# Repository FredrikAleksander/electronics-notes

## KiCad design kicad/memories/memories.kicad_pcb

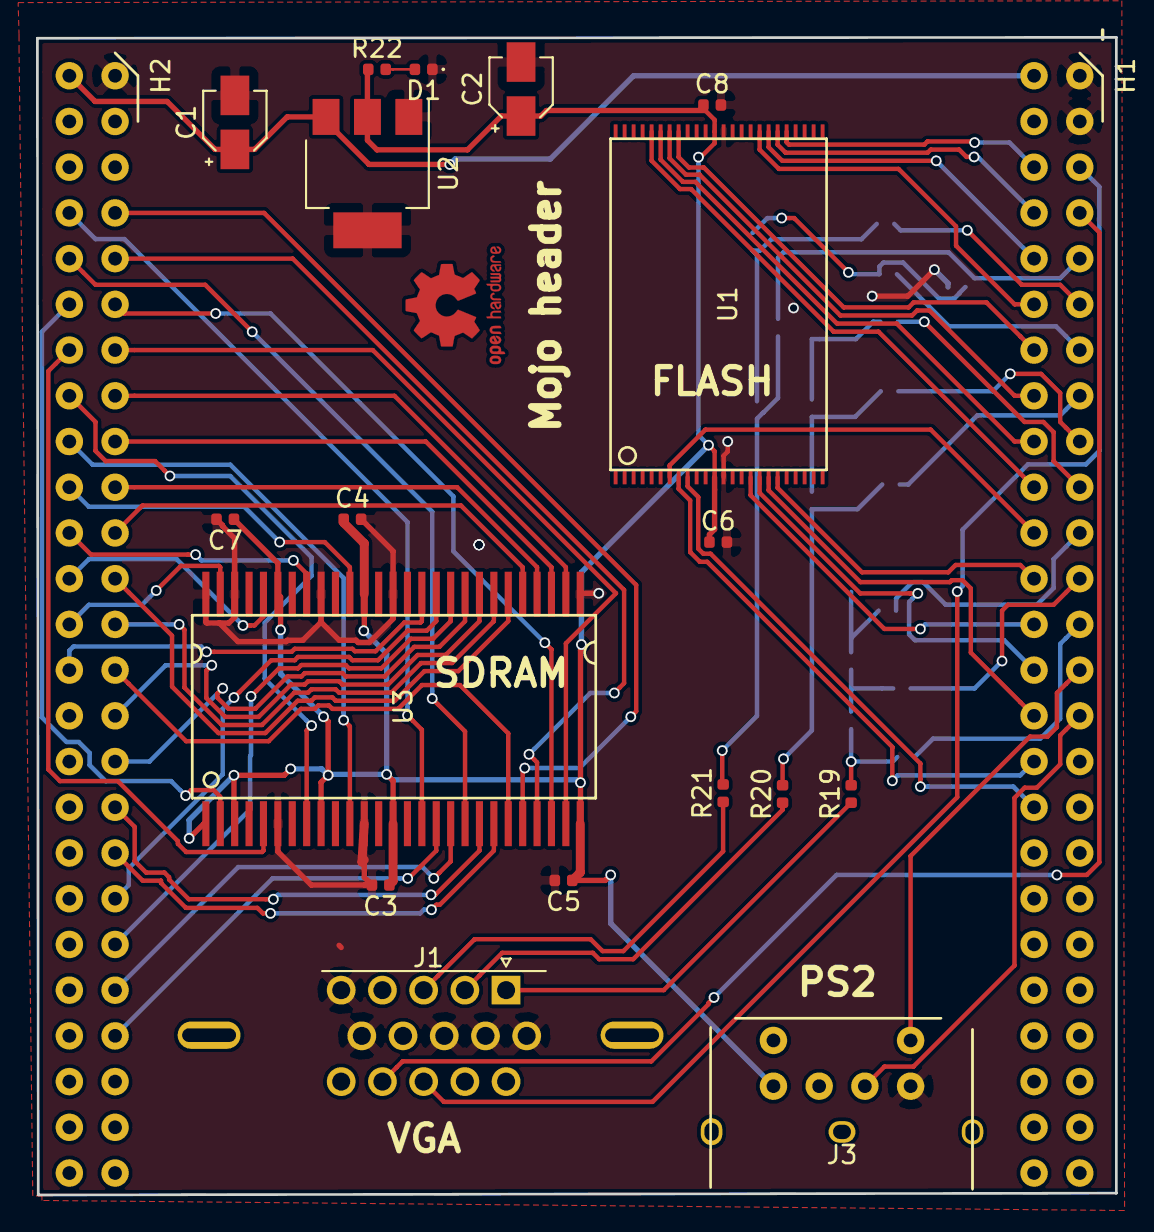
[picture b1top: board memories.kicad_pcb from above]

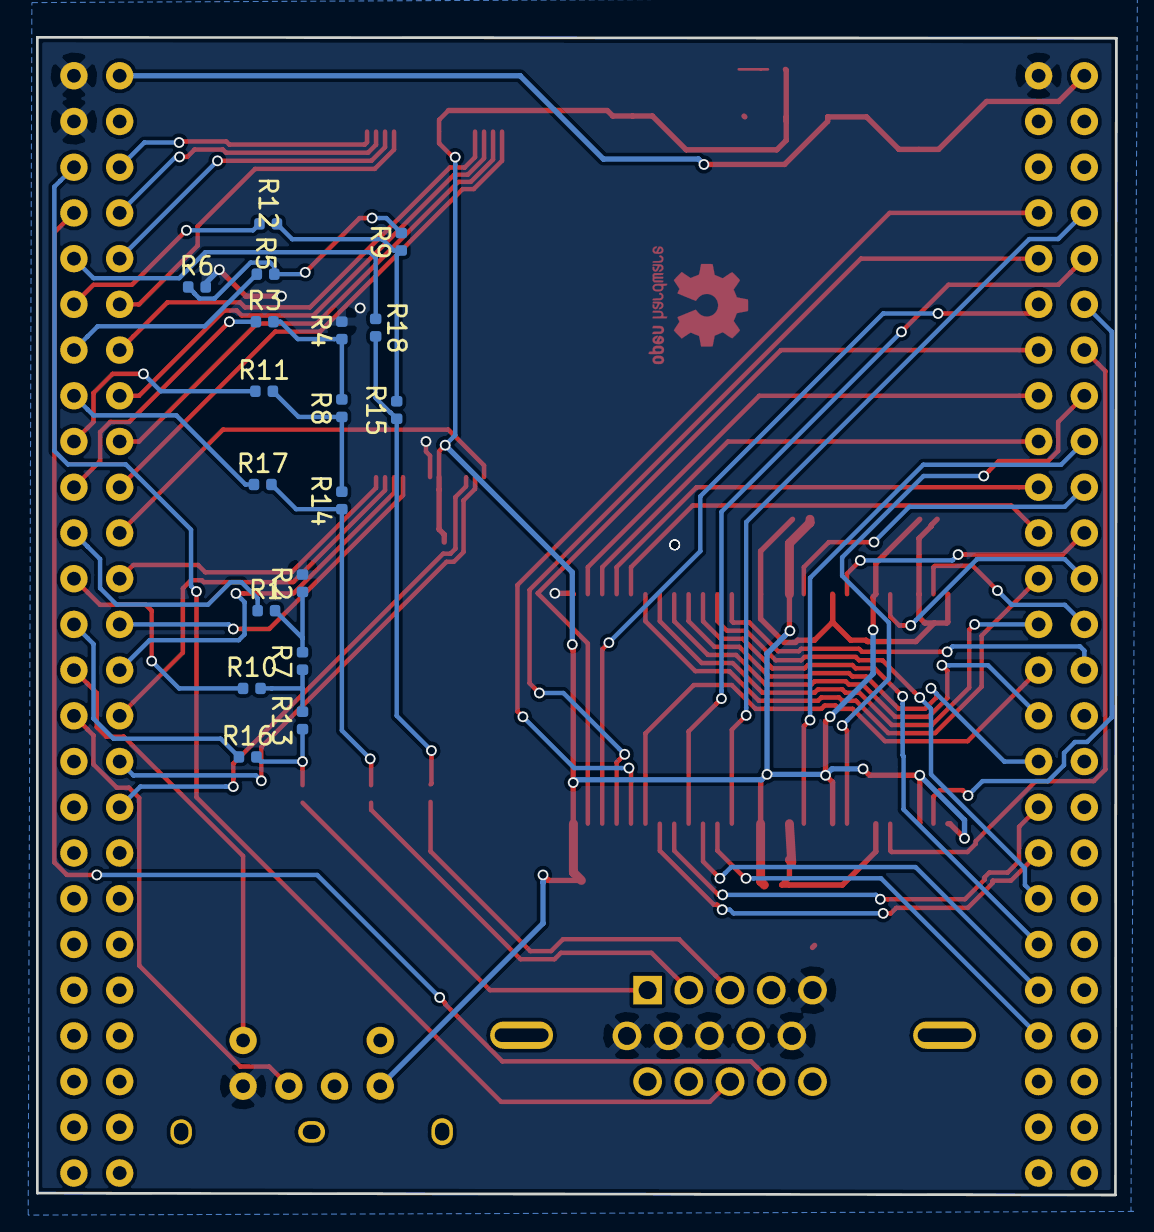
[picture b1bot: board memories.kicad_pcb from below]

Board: 2 copper layers, 59.9 x 64.3 mm, 38 parts (18 on the bottom side), 74 nets.

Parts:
C1, C2: CP1; CP_Elec_3x5.3
C3, C4, C5, C6, C7, C8: C; C_0402_1005Metric
D1: LED; LED_0402_1005Metric
H1: Header; mojo_header
H2: mojo_header_lower; mojo_header
J1: DB15_Female_HighDensity; DSUB-15-HD_Female
J3: DIN-6; mini-DIN6
R1, R2, R3, R4, R5, R6, R7, R8, R9, R10, R11, R12, R13, R14, R15, R16, R17, R18, R19, R20, R21, R22: R; R_0402_1005Metric
U1: NAND512
U2: AMS1117-3V3; SOT-223
U3: MT48LC32M8A2; TSOP_54

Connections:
3V3: C2.1, C3.1, C4.1, C5.1, C6.1, C7.1, C8.1, J3.4, R22.1, U1.12, U1.37, U2.2, U3.1, U3.3, U3.9, U3.14, U3.27, U3.43, U3.49
/DQ0: H2.31, U3.2
/DQ1: H2.32, U3.5
/DQ2: H2.33, U3.8
/DQ3: H2.34, U3.11
/DQ4: H2.35, U3.44
/DQ5: H2.36, U3.47
/DQ6: H2.37, U3.50
/DQ7: H2.38, U3.53
/VGA/VGA_B0: H1.5, R18.1
/VGA/VGA_B1: H1.6, R12.1
/VGA/VGA_B2: H1.7, R5.1
/VGA/VGA_B_OUT: J1.3, R21.1
/VGA/VGA_G0: H1.8, R17.1
/VGA/VGA_G1: H1.9, R11.1
/VGA/VGA_G2: H1.10, R3.1
/VGA/VGA_G_OUT: J1.2, R20.1
/VGA/VGA_HSYNC: H1.3, J1.13
/VGA/VGA_R0: H1.13, R16.1
/VGA/VGA_R1: H1.12, R10.1
/VGA/VGA_R2: H1.11, R1.1
/VGA/VGA_R_OUT: J1.1, R19.1
/VGA/VGA_VSYNC: H1.4, J1.14
DQM: H2.39, U3.39
GND: C1.2, C2.2, C3.2, C4.2, C5.2, C6.2, C7.2, C8.2, D1.1, H1.1, H1.2, H2.1, J1.5, J1.6, J1.7, J1.8, J1.10, J3.3, R2.2, R4.2, R6.2, U1.13, U1.36, U2.1, U2.4, U3.6, U3.12, U3.28, U3.41, U3.46, U3.52, U3.54
unnamed: D1.2, R22.2
unnamed: H1.28, U1.29
unnamed: H1.29, U1.30
unnamed: H1.30, U1.31
unnamed: H1.31, U1.32
unnamed: H1.32, U1.41
unnamed: H1.33, U1.42
unnamed: H1.34, U1.43
unnamed: H1.35, U1.44
unnamed: H1.36, U1.7
unnamed: H1.37, U1.19
unnamed: H1.38, U1.16
unnamed: H1.39, U1.17
unnamed: H1.40, U1.18
unnamed: H1.41, U1.8
unnamed: H1.42, U1.9
unnamed: H2.4, U3.23
unnamed: H2.5, U3.24
unnamed: H2.6, U3.25
unnamed: H2.7, U3.26
unnamed: H2.8, U3.29
unnamed: H2.9, U3.30
unnamed: H2.10, U3.31
unnamed: H2.11, U3.32
unnamed: H2.12, U3.33
unnamed: H2.13, U3.34
unnamed: H2.14, U3.22
unnamed: H2.15, U3.35
unnamed: H2.16, U3.36
unnamed: H2.17, U3.20
unnamed: H2.18, U3.21
unnamed: H2.19, U3.38
unnamed: H2.20, U3.37
unnamed: H2.21, U3.18
unnamed: H2.22, U3.17
unnamed: H2.29, U3.16
unnamed: H2.30, U3.19
unnamed: R1.2, R2.1, R7.2
unnamed: R3.2, R4.1, R8.2
unnamed: R5.2, R6.1, R9.2
unnamed: R7.1, R10.2, R13.2
unnamed: R8.1, R11.2, R14.2
unnamed: R9.1, R12.2, R15.2
unnamed: R13.1, R16.2, R19.2
unnamed: R14.1, R17.2, R20.2
unnamed: R15.1, R18.2, R21.2
PS2_CLK: H1.14, J3.5
PS2_DATA: H1.15, J3.1
V_EXTERNAL: C1.1, H1.26, H2.26, U2.3

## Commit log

2018-07-15 kicad: add mojo shield.
    It contains SDRAM, Flash, VGA and PS2.
